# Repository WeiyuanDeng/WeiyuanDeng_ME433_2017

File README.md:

Weiyuan Deng
04-06-2017
This is a repository for ME 433 at Northwestern University
Add a line to test

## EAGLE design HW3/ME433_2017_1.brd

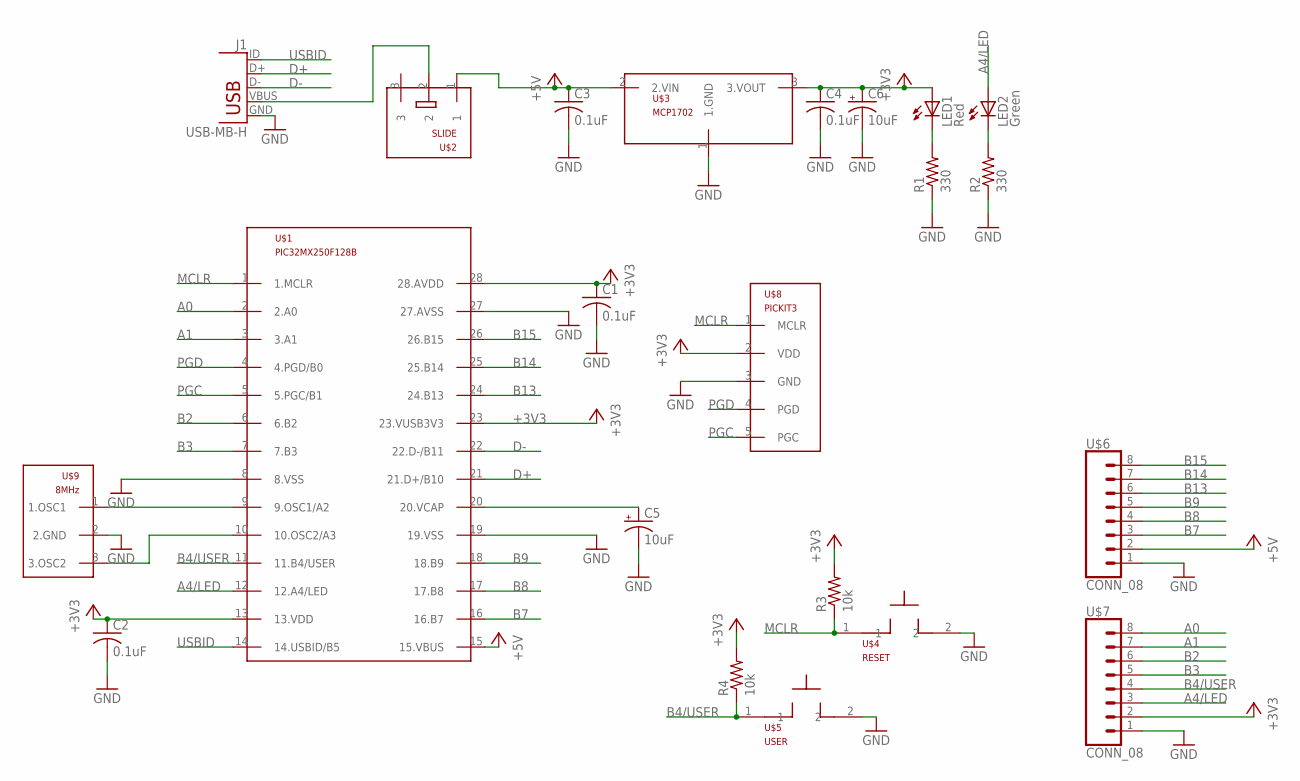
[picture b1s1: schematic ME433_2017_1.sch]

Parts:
C1, C2, C3, C4: 0.1uF; C025-025X050
C5, C6: 10uF; B45181B
J1: USB-MB-H
LED1: Red; LED3MM
LED2: Green; LED3MM
R1, R2: 330; 0207/10
R3, R4: 10k; 0207/10
U$1: PIC32MX250F128B; DIL28-3
U$2: SLIDE
U$3: MCP1702; TO92
U$4: RESET; PB
U$5: USER; PB
U$6, U$7: CONN_08; 1X08
U$8: PICKIT3; 1X05
U$9: 8MHz; OSC

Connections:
+3V3: C1.1, C2.1, C4.1, C6.+, LED1.A, R3.2, R4.2, U$1.13 (13.VDD), U$1.23 (23.VUSB3V3), U$1.28 (28.AVDD), U$3.3 (3.VOUT), U$7.2, U$8.2 (VDD)
+5V: C3.1, U$1.15 (15.VBUS), U$2.1, U$3.2 (2.VIN), U$6.2
A0: U$1.2 (2.A0), U$7.8
A1: U$1.3 (3.A1), U$7.7
A4/LED: LED2.A, U$1.12 (12.A4/LED), U$7.3
B2: U$1.6 (6.B2), U$7.6
B3: U$1.7 (7.B3), U$7.5
B4/USER: R4.1, U$1.11 (11.B4/USER), U$5.1, U$7.4
B7: U$1.16 (16.B7), U$6.3
B8: U$1.17 (17.B8), U$6.4
B9: U$1.18 (18.B9), U$6.5
B13: U$1.24 (24.B13), U$6.6
B14: U$1.25 (25.B14), U$6.7
B15: U$1.26 (26.B15), U$6.8
D+: J1.D+, U$1.21 (21.D+/B10)
D-: J1.D-, U$1.22 (22.D-/B11)
GND: C1.2, C2.2, C3.2, C4.2, C5.-, C6.-, J1.GND, R1.1, R2.1, U$1.8 (8.VSS), U$1.19 (19.VSS), U$1.27 (27.AVSS), U$3.1 (1.GND), U$4.2, U$5.2, U$6.1, U$7.1, U$8.3 (GND), U$9.2 (2.GND)
MCLR: R3.1, U$1.1 (1.MCLR), U$4.1, U$8.1 (MCLR)
unnamed: J1.VBUS, U$2.2
unnamed: LED2.K (C), R2.2
unnamed: LED1.K (C), R1.2
unnamed: U$1.9 (9.OSC1/A2), U$9.1 (1.OSC1)
unnamed: U$1.10 (10.OSC2/A3), U$9.3 (3.OSC2)
unnamed: C5.+, U$1.20 (20.VCAP)
PGC: U$1.5 (5.PGC/B1), U$8.5 (PGC)
PGD: U$1.4 (4.PGD/B0), U$8.4 (PGD)
USBID: J1.ID, U$1.14 (14.USBID/B5)

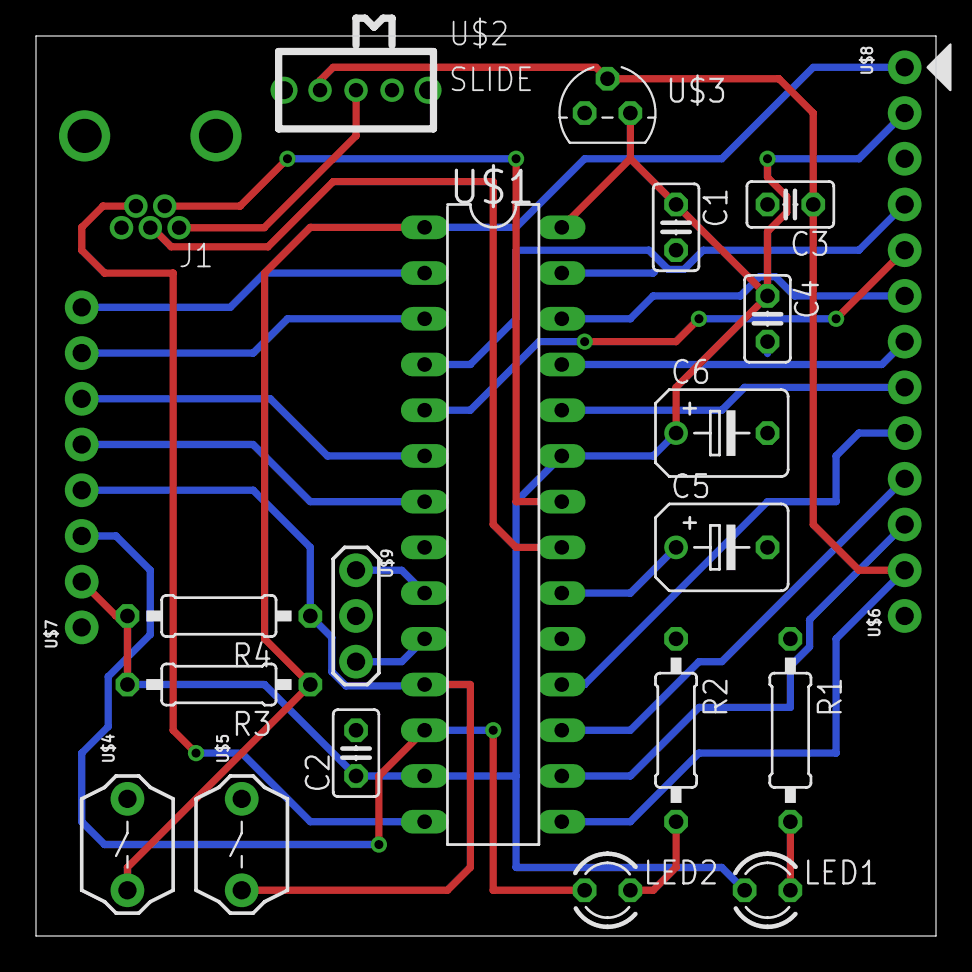
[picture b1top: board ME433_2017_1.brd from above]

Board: 2 copper layers, 50.0 x 50.0 mm, 22 parts (0 on the bottom side), 27 nets.

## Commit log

2017-04-06 :lollipop: Added .gitattributes & .gitignore files
2017-04-06 Add README.md
2017-04-06 Add a line to test
2017-04-08 Add 。；br
2017-04-08 remove
2017-04-08 HW2 Add the .lbr file
2017-04-08 HW2 Add the .sch file
2017-04-08 Add the .brd file
    The board looks complete, but got errors that can't figure out so far.
2017-04-13 Add photos of the breadboard
2017-04-17 Add schematic image
2017-04-17 Add lbr and sch file to HW3
2017-04-17 Add Gerber files
2017-04-17 Add image of the board
2017-04-18 Add schematic
2017-04-18 Add code hw1.c
2017-04-18 Add project HW1
2017-04-18 Add nscope screen shots
2017-05-08 Initialize the HelloWorld Android Project
2017-05-08 Add slider bar and text, etc
2017-05-09 Add photos of the app SayHello
2017-05-15 Initialize the project, give the app camera permission
2017-05-15 Change java file
2017-05-15 Update texture on green surface
2017-05-20 Add images and stl file of the wheel
2017-05-20 Add images of the green detection app
2017-05-21 Correct the outer diameter for the wheel
2017-05-21 Add the gcode of the wheel
2017-06-06 Changes of HW1
2017-06-06 Add dxf file of the box
2017-06-06 Add HW4 project
2017-06-06 Add breadboard image of HW4
2017-06-06 Add gcode of wheel with no support
2017-06-06 Add cura image of the wheel
2017-06-06 Add schematic for HW4
2017-06-06 Add schematic for HW5
2017-06-06 Add breadboard for HW5
2017-06-06 Add project for HW5
2017-06-07 Add car chassis design
2017-06-07 Add new bracket
2017-06-07 Add HW6 project
2017-06-07 Add HW6 code
2017-06-07 Add breadboard image
2017-06-07 Add project HW7
2017-06-07 Add initial code
2017-06-07 laser cutting
2017-06-08 Add Android part of HW14
2017-06-08 Add android stuff
2017-06-08 Add pic part
2017-06-09 The libs and some code accidently gone, not sure why, redid HW14
2017-06-10 Add APP for HW19
2017-06-10 Add the follow line APP to HW20
2017-06-10 Add image of app
2017-06-10 clean up
2017-06-10 Add Project HW
2017-06-10 Add Project HW10
2017-06-10 Clean up HW5
2017-06-10 Clean up HW6
2017-06-10 HW7 small change update
2017-06-10 Add HW8 harmony project
2017-06-10 initialize
2017-06-10 Add image of HW8
2017-06-10 Upload HW9
2017-06-10 Add image
2017-06-10 add hw 11 hasn‘t finish
2017-06-10 Add image of the car
2017-06-10 Add image of the box
2017-06-10 Add PWM code for HW18
